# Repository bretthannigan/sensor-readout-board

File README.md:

# Sensor Readout Board

This repository includes the software, firmware, and hardware for the readout electronics used in the paper:

> B. C. Hannigan, T. J. Cuthbert, C. Admadizadeh, and C. Menon, _Distributed Sensing Along Fibres for Smart Clothing_. April 2023. [Preprint]

## Python Client

The `Client` subfolder contains the source code for the PC client, written in Python. The client allows connection to the FPGA and optional logging of data. The data can be interpreted in a variety of formats, such as:
- `raw`: raw ADC counts (32-bit signed integer)
- `iq`: impedances expressed as in-phase and quadrature components (equivalently, real and imagingary impedance components) in Ohms.
- `magphase`: impedances expressed as magnitude (in dB) and phase (in degrees).
- `RCseries`: impedances converted to resistance and capacitance values in an RC series circuit.
- `RCparallel`: impedances converted to resistance and capacitance values in an RC parallel circuit.
- `model`: (experimental) processed signals using a provided model (e.g., from sklearn or Keras) to convert the raw signals into a measure of interest.
Command-line arguments exist to control the COM port and logfile destination. One can also enable or disable the plotting of data to the screen and triggering ability. Note that the correct gain that matches the jumper on the PCB must be supplied via command-line argument for the scaling to be correct. There also exist some calibration curves as Excel spreadsheets.

## FPGA Firmware

The `Firmware` folder contains many general-purpose logic buliding blocks such as counters, FIFOs, memories, etc. and associated test-benches. The `Firmware/top` subfolder contains the top-level Verilog file `top.v` which was used for the data collection in the paper. This relies directly on the following third-party libraries:
- `verilog-lfsr` by Alex Forencich: https://github.com/alexforencich/verilog-lfsr. Used to implement the linear-feedback shift register that enables redundancy checking for the MIN protocol serial packets.
- `osdvu/uart` by Timothy Goddard: https://github.com/cyrozap/osdvu. Used to implement the UART.
- `min-protocol` by Ken Tindell: https://github.com/min-protocol/min. Used to frame the data sent to the PC.

## Hardware

The `Hardware/Enclosure` subfolder contains Solidworks files for the system enclosure. These were printed on a FDM 3D printer. The `Hardware/PCB` subfolder contains PCB schematic and layout files from KiCAD. The other subfolders contain (disorganized) SPICE simulations, previous iterations, and other files used during development.

©2023 ETH Zurich, Brett Hannigan; D-HEST; Biomedical and Mobile Health Technology (BMHT) Lab; Carlo Menon

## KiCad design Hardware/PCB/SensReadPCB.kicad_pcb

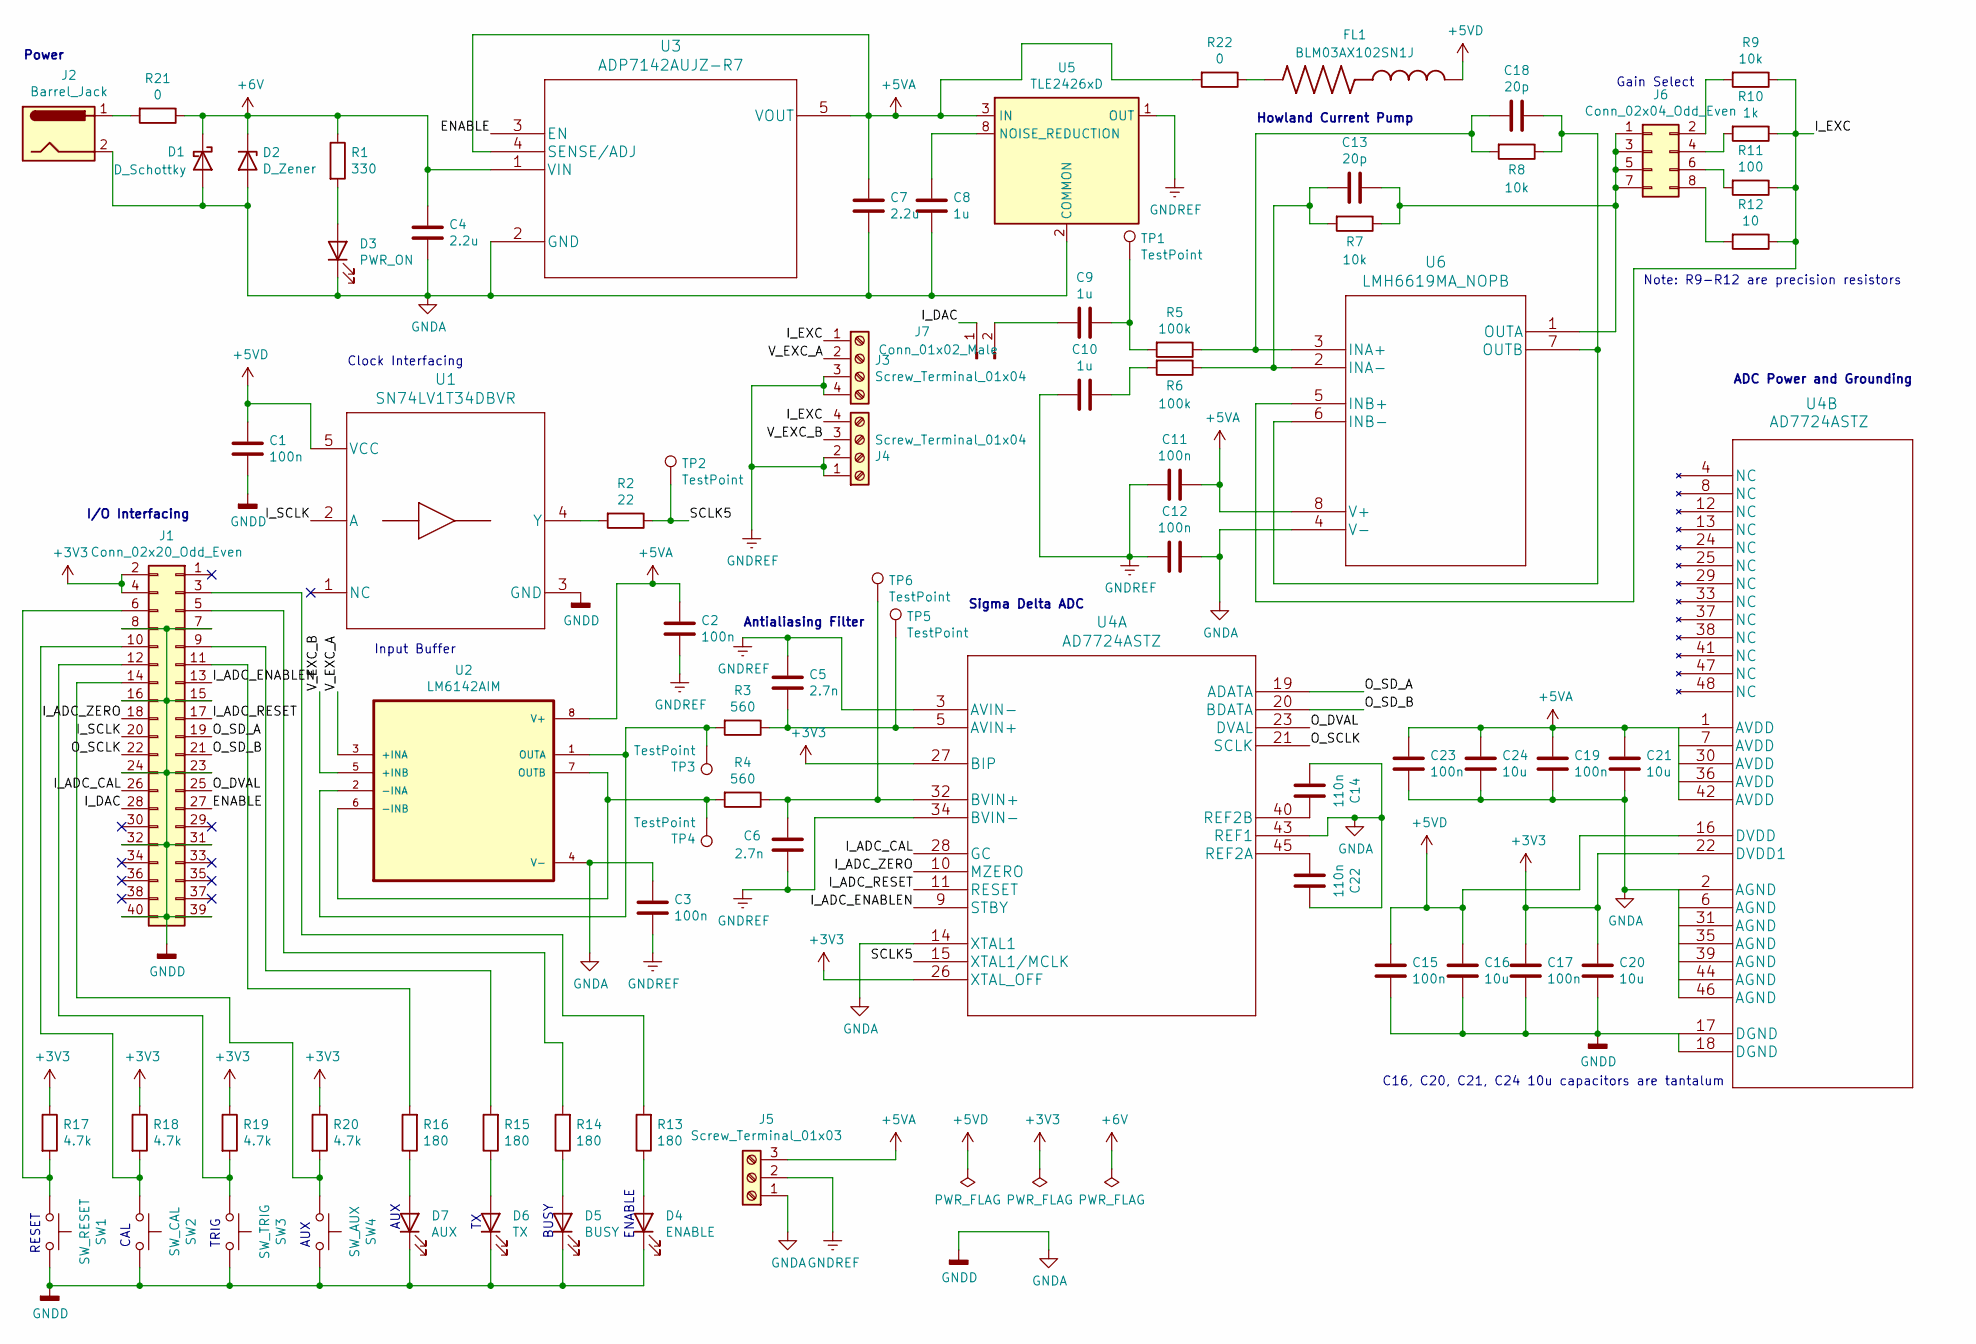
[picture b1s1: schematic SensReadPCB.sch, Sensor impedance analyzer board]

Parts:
C1, C2, C3, C11, C12, C15, C17, C19, C23: 100n; C_0603_1608Metric_Pad1.08x0.95mm_HandSolder
C4, C7: 2.2u; C_0603_1608Metric_Pad1.08x0.95mm_HandSolder
C5, C6: 2.7n; C_0603_1608Metric_Pad1.08x0.95mm_HandSolder
C8, C9, C10: 1u; C_0603_1608Metric_Pad1.08x0.95mm_HandSolder
C13, C18: 20p; C_0603_1608Metric_Pad1.08x0.95mm_HandSolder
C14, C22: 110n; C_0603_1608Metric_Pad1.08x0.95mm_HandSolder
C16, C20, C21, C24: 10u; C_0603_1608Metric_Pad1.08x0.95mm_HandSolder
D1: D_Schottky; D_SOD-323_HandSoldering
D2: D_Zener; D_SOD-323_HandSoldering
D3: PWR_ON; D_0603_1608Metric_Pad1.05x0.95mm_HandSolder
D4: ENABLE; D_0603_1608Metric_Pad1.05x0.95mm_HandSolder
D5: BUSY; D_0603_1608Metric_Pad1.05x0.95mm_HandSolder
D6: TX; D_0603_1608Metric_Pad1.05x0.95mm_HandSolder
D7: AUX; D_0603_1608Metric_Pad1.05x0.95mm_HandSolder
FL1: BLM03AX102SN1J; BEADC0603X33N
J1: Conn_02x20_Odd_Even; PinHeader_2x20_P2.54mm_Vertical
J2: Barrel_Jack; KLDX-0202-A
J3, J4: Screw_Terminal_01x04; TerminalBlock_Phoenix_MPT-0,5-4-2.54_1x04_P2.54mm_Horizontal
J5: Screw_Terminal_01x03; PinSocket_1x03_P2.54mm_Vertical
J6: Conn_02x04_Odd_Even; PinHeader_2x04_P2.54mm_Vertical
J7: Conn_01x02_Male; PinHeader_1x02_P2.54mm_Vertical
R1: 330; R_0603_1608Metric_Pad0.98x0.95mm_HandSolder
R2: 22; R_0603_1608Metric_Pad0.98x0.95mm_HandSolder
R3, R4: 560; R_0603_1608Metric_Pad0.98x0.95mm_HandSolder
R5, R6: 100k; R_0603_1608Metric_Pad0.98x0.95mm_HandSolder
R7, R8, R9: 10k; R_0603_1608Metric_Pad0.98x0.95mm_HandSolder
R10: 1k; R_0603_1608Metric_Pad0.98x0.95mm_HandSolder
R11: 100; R_0603_1608Metric_Pad0.98x0.95mm_HandSolder
R12: 10; R_0603_1608Metric_Pad0.98x0.95mm_HandSolder
R13, R14, R15, R16: 180; R_0603_1608Metric_Pad0.98x0.95mm_HandSolder
R17, R18, R19, R20: 4.7k; R_0603_1608Metric_Pad0.98x0.95mm_HandSolder
R21, R22: 0; R_0603_1608Metric_Pad0.98x0.95mm_HandSolder
SW1: SW_RESET; PTS636_SMTR
SW2: SW_CAL; PTS636_SMTR
SW3: SW_TRIG; PTS636_SMTR
SW4: SW_AUX; PTS636_SMTR
TP1, TP2, TP3, TP4, TP5, TP6: TestPoint; TestPoint_THTPad_2.5x2.5mm_Drill1.2mm
U1: SN74LV1T34DBVR
U2: LM6142AIM
U3: ADP7142AUJZ-R7
U4: AD7724ASTZ
U5: TLE2426xD; SOIC-8_3.9x4.9mm_P1.27mm
U6: LMH6619MA_NOPB; LMH6619MA

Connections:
+3V3: C17.1, C20.1, J1.2, J1.4, R17.1, R18.1, R19.1, R20.1, U4.22 (DVDD1), U4.26 (XTAL_OFF), U4.27 (BIP)
+5VA: C2.1, C7.1, C11.1, C19.1, C21.1, C23.1, C24.1, J5.3, R22.2, U2.8 (V+), U3.4 (SENSE/ADJ), U3.5 (VOUT), U4.1 (AVDD), U4.7 (AVDD), U4.30 (AVDD), U4.36 (AVDD), U4.42 (AVDD), U5.3 (IN), U6.8 (V+)
+5VD: C1.1, C15.1, C16.1, FL1.1, U1.5 (VCC), U4.16 (DVDD)
+6V: C4.1, D1.1 (K), D2.1 (K), R1.1, R21.1, U3.1 (VIN)
/ENABLE: J1.27, U3.3 (EN)
/I_ADC_CAL: J1.26, U4.28 (GC)
/I_ADC_ENABLEN: J1.13, U4.9 (STBY)
/I_ADC_RESET: J1.17, U4.11 (RESET)
/I_ADC_ZERO: J1.18, U4.10 (MZERO)
/I_DAC: J1.28, J7.1
/I_EXC: J3.1, J4.4, R9.1, R10.1, R11.1, R12.1, U6.5 (INB+)
/I_SCLK: J1.20, U1.2 (A)
/O_DVAL: J1.25, U4.23 (DVAL)
/O_SCLK: J1.22, U4.21 (SCLK)
/O_SD_A: J1.19, U4.19 (ADATA)
/O_SD_B: J1.21, U4.20 (BDATA)
/SCLK5: R2.1, TP2.1, U4.15 (XTAL1/MCLK)
/V_EXC_A: J3.2, U2.3 (+INA)
/V_EXC_B: J4.3, U2.5 (+INB)
GNDA: C1.2, C3.1, C4.2, C7.2, C8.2, C12.1, C14.2, C15.2, C16.2, C17.2, C19.2, C20.2, C21.2, C22.1, C23.2, C24.2, D1.2 (A), D2.2 (A), D3.1 (K), D4.1 (K), D5.1 (K), D6.1 (K), D7.1 (K), J1.7, J1.8, J1.15, J1.16, J1.23, J1.24, J1.31, J1.32, J1.39, J1.40, J2.2, J5.1, SW1.2, SW2.2, SW3.2, SW4.2, U1.3 (GND), U2.4 (V-), U3.2 (GND), U4.2 (AGND), U4.6 (AGND), U4.14 (XTAL1), U4.17 (DGND), U4.18 (DGND), U4.31 (AGND), U4.35 (AGND), U4.39 (AGND), U4.43 (REF1), U4.44 (AGND), U4.46 (AGND), U5.2 (COMMON), U6.4 (V-)
GNDREF: C2.2, C3.2, C5.1, C6.2, C10.2, C11.2, C12.2, J3.3, J3.4, J4.1, J4.2, J5.2, U4.3 (AVIN-), U4.34 (BVIN-), U5.1 (OUT)
unnamed: C5.2, R3.1, TP5.1, U4.5 (AVIN+)
unnamed: C6.1, R4.1, TP6.1, U4.32 (BVIN+)
unnamed: C8.1, U5.8 (NOISE_REDUCTION)
unnamed: C9.1, R5.2, TP1.1
unnamed: C9.2, J7.2
unnamed: C10.1, R6.2
unnamed: C13.1, J6.1, J6.3, J6.5, J6.7, R7.1, U6.1 (OUTA)
unnamed: C13.2, R6.1, R7.2, U6.2 (INA-)
unnamed: C14.1, U4.40 (REF2B)
unnamed: C18.1, R8.1, U6.6 (INB-), U6.7 (OUTB)
unnamed: C18.2, R5.1, R8.2, U6.3 (INA+)
unnamed: C22.2, U4.45 (REF2A)
unnamed: D3.2 (A), R1.2
unnamed: D4.2 (A), R13.1
unnamed: D5.2 (A), R14.1
unnamed: D6.2 (A), R15.1
unnamed: D7.2 (A), R16.1
unnamed: FL1.2, R22.1
unnamed: J1.3, R13.2
unnamed: J1.5, R14.2
unnamed: J1.6, R17.2, SW1.1
unnamed: J1.9, R15.2
unnamed: J1.10, R18.2, SW2.1
unnamed: J1.11, R16.2
unnamed: J1.12, R19.2, SW3.1
unnamed: J1.14, R20.2, SW4.1
unnamed: J2.1, R21.2
unnamed: J6.2, R9.2
unnamed: J6.4, R10.2
unnamed: J6.6, R11.2
unnamed: J6.8, R12.2
unnamed: R2.2, U1.4 (Y)
unnamed: R3.2, TP3.1, U2.1 (OUTA), U2.2 (-INA)
unnamed: R4.2, TP4.1, U2.6 (-INB), U2.7 (OUTB)

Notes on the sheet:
Sigma Delta ADC
Antialiasing Filter
ADC Power and Grounding
Howland Current Pump
Power
Clock Interfacing
Input Buffer
I/O Interfacing
Note: R9-R12 are precision resistors
ENABLE
BUSY
TRIG
CAL
RESET
AUX
Gain Select
C16, C20, C21, C24 10u capacitors are tantalum

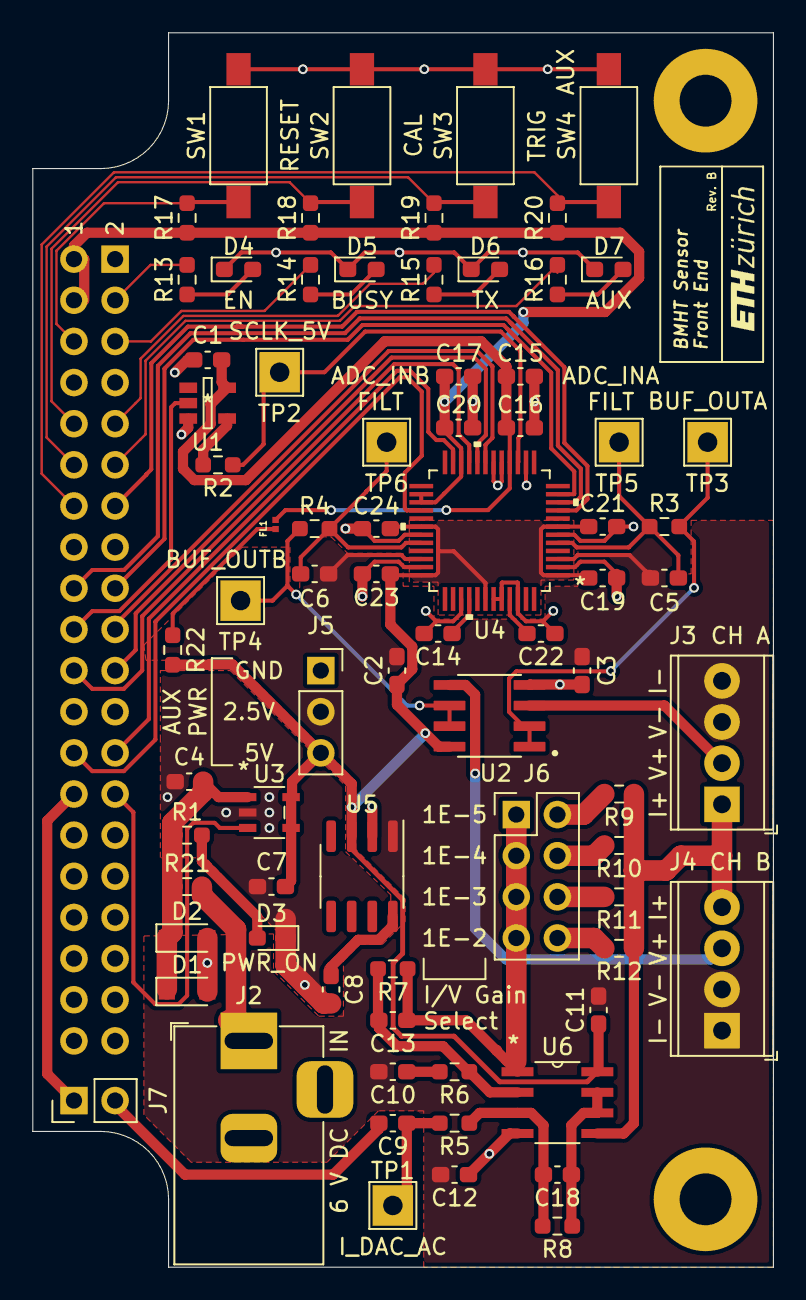
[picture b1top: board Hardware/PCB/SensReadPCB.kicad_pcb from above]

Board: 2 copper layers, 45.7 x 76.2 mm, 77 parts (1 on the bottom side), 55 nets.

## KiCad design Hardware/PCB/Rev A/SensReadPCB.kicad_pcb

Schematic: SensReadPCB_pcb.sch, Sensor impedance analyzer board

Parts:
C1, C2: 20p; C_1206_HandSoldering
C3, C4, C5, C8, C9, C19, C20: 100n; C_1206_HandSoldering
C6, C11: 1u; C_1206_HandSoldering
C7, C10: 10n; C_1206_HandSoldering
C12: 680p; C_1206_HandSoldering
C13: 1.5n; C_1206_HandSoldering
C14, C15, C16: 130p; C_1206_HandSoldering
C17: 390p; C_1206_HandSoldering
C18: C; C_1206_HandSoldering
D1, D3: D_Schottky; D_1206
D2, D6: D_Zener; D_1206
D4: PWR_ON; LED_1206_HandSoldering
D5: ENABLE; LED_1206_HandSoldering
J1: Barrel_Jack; BARREL_JACK
J2: Conn_02x20_Odd_Even; Pin_Header_Straight_2x20_Pitch2.54mm
J3: Conn_02x04_Odd_Even; Pin_Header_Straight_2x04_Pitch2.54mm
J4: Screw_Terminal_01x04; TerminalBlock_Phoenix_MPT-2.54mm_4pol
R1, R2: 100k; R_1206_HandSoldering
R3, R4, R5: 10k; R_1206_HandSoldering
R6, R18: 1k; R_1206_HandSoldering
R7: 100; R_1206_HandSoldering
R8: 10; R_1206_HandSoldering
R9: 4.75k; R_1206_HandSoldering
R10: 13.7k; R_1206_HandSoldering
R11: 14.0k; R_1206_HandSoldering
R12: 750; R_1206_HandSoldering
R13: 806; R_1206_HandSoldering
R14: 4.64k; R_1206_HandSoldering
R15: 1.10k; R_1206_HandSoldering
R16: 6.98k; R_1206_HandSoldering
R17: 68; R_1206_HandSoldering
R19: 510; R_1206_HandSoldering
R20, R21: 0R; R_1206_HandSoldering
R22, R29: 0; R_1206_HandSoldering
R23: 5.11k; R_1206_HandSoldering
R24, R27: 28k; R_1206_HandSoldering
R25: 1.58meg; R_1206_HandSoldering
R26: 68.1k; R_1206_HandSoldering
R28: 5.36k; R_1206_HandSoldering
RV1: 10k; 23BR50KLFTR
RV2: 47k; 23BR50KLFTR
TP1: DAC_AC; Measurement_Point_Square-TH_Big
TP2: LF_1; Measurement_Point_Square-TH_Big
TP3: LF_2; Measurement_Point_Square-TH_Big
TP4: LF_3; Measurement_Point_Square-TH_Big
TP5: LF_4; Measurement_Point_Square-TH_Big
TP6: ADC_OUT; Measurement_Point_Square-TH_Big
TP7, TP8: TestPoint; Measurement_Point_Square-TH_Big
U1: LMH6619MA_NOPB; LMH6619MA&slash_NOPB
U2: MAX903CSA+; MAX903CSA&plus_
U3: LP2985A-10DBVR
U4: TLE2426xD; TLE2426CD
U5: LM6144AIM_NOPB; LM6144AIM&slash_NOPB

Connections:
+3V3: C3.1, J2.2, J2.4, U2.5, U2.8
+5V: C6.1, D1.1 (K), D2.1 (K), J1.1, R19.1, U3.1
+5VA: C4.1, C8.1, C10.1, C19.1, U1.8, U2.1, U3.5, U4.3 (IN), U5.4
-5V: C5.1, C6.2, C7.2, C9.1, C10.2, C11.2, C20.1, D1.2 (A), D2.2 (A), D4.1 (K), J1.2, U1.4, U2.4, U3.2, U4.2 (COMMON), U5.11
/ADC_2_Y: C13.2, R14.1, R21.2, R29.2, TP4.1, U5.8
/ADC_4_Y: C14.2, R20.2, R24.1, R25.2, TP5.1, U5.14
/ADC_FB_N: J2.6, RV2.2
/ADC_FB_P: J2.5, RV1.1
/ADC_FB_S_N: C12.2, R9.2, R11.2, R14.2, RV1.2, TP7.1, U5.2
/ADC_FB_S_P: RV2.3, TP8.1, U5.3
/ADC_OUT: J2.3, R18.2, TP6.1, U2.7
/CLK: J2.10
/DAC_IN: C18.2, J2.11
/ENABLE: J2.1, R17.2, U3.3
/I_EXC: J4.1, R5.1, R6.1, R7.1, R8.1, U1.5
/S_CLK: J2.9
/V_EXC: J4.2, R9.1, R10.2, R16.1
GNDA: C3.2, C4.2, C5.2, C8.2, C9.2, C17.1, C19.2, C20.2, D3.2 (A), D5.1 (K), D6.2 (A), J2.7, J2.8, J4.3, J4.4, R2.2, R22.2, R23.1, RV2.1, U2.3, U2.6, U4.1 (OUT), U5.5, U5.10, U5.12
unnamed: C1.1, J3.1, J3.3, J3.5, J3.7, R3.1, U1.1
unnamed: C1.2, R2.1, R3.2, U1.2
unnamed: C2.1, R4.1, U1.6, U1.7
unnamed: C2.2, R1.1, R4.2, U1.3
unnamed: C7.1, U3.4
unnamed: C11.1, U4.8 (NOISE_REDUCTION)
unnamed: C12.1, R11.1, R12.2, TP2.1, U5.1
unnamed: C13.1, R15.1, R16.2, U5.9
unnamed: C14.1, C15.1, C16.2, R23.2, R26.2
unnamed: C15.2, R26.1, R28.1, R29.1
unnamed: C16.1, R22.1, R25.1, R27.2, U5.13
unnamed: C17.2, R24.2, R27.1, R28.2
unnamed: C18.1, R1.2, TP1.1
unnamed: D3.1 (K), D6.1 (K), R18.1
unnamed: D4.2 (A), R19.2
unnamed: D5.2 (A), R17.1
unnamed: J3.2, R5.2
unnamed: J3.4, R6.2
unnamed: J3.6, R7.2
unnamed: J3.8, R8.2
unnamed: R10.1, R12.1, R13.1, U5.6
unnamed: R13.2, R15.2, TP3.1, U5.7
unnamed: R20.1, R21.1, U2.2

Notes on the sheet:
Gain Select
Howland Current Source
Power Conditioning
Interfacing
Comparator
Single-amplifier biquad
ADC Loop Filter
Fleisher-Tow biquad
Set: R21 15k R32 32k
Set: R21 4.7k

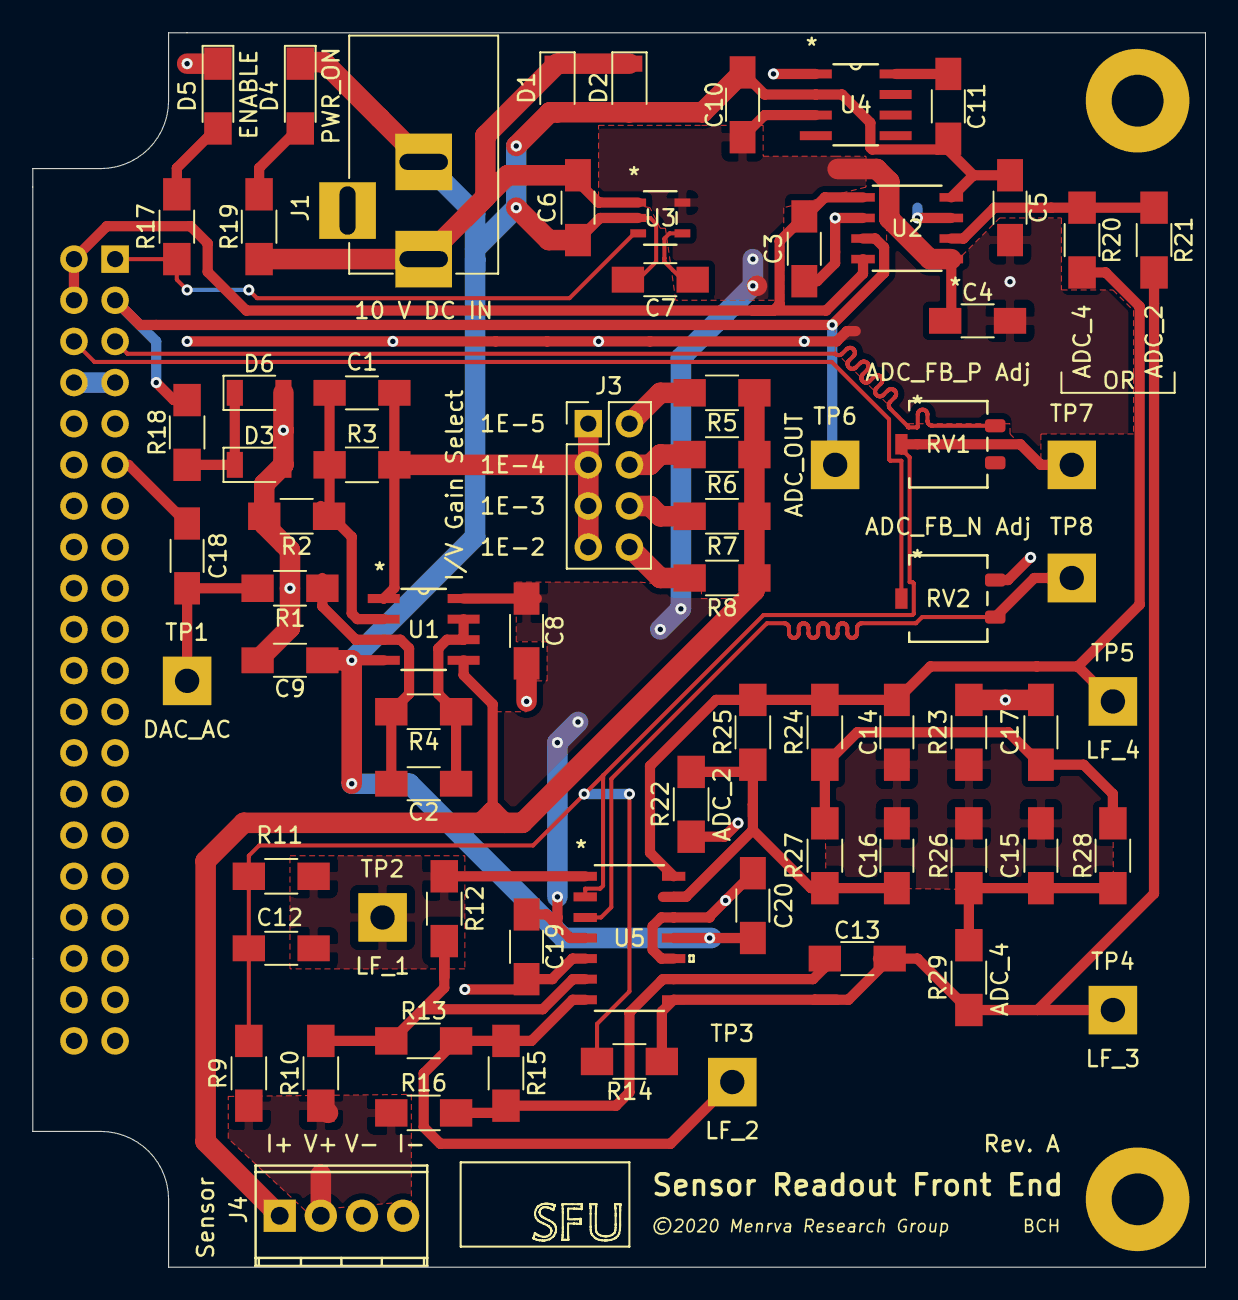
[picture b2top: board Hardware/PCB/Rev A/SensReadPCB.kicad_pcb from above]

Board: 2 copper layers, 72.4 x 76.2 mm, 74 parts (1 on the bottom side), 39 nets.

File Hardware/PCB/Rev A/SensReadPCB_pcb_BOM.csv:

Reference, Value, Footprint, Datasheet,Done
U1,LMH6619MA_NOPB,LMH6619MA:LMH6619MA&slash_NOPB,,TRUE
R1,100k,Resistors_SMD:R_1206_HandSoldering,~,TRUE
R2,100k,Resistors_SMD:R_1206_HandSoldering,~,TRUE
R3,10k,Resistors_SMD:R_1206_HandSoldering,~,TRUE
C1,20p,Capacitors_SMD:C_1206_HandSoldering,~,TRUE
R4,10k,Resistors_SMD:R_1206_HandSoldering,~,TRUE
C2,20p,Capacitors_SMD:C_1206_HandSoldering,~,TRUE
J3,Conn_02x04_Odd_Even,Pin_Headers:Pin_Header_Straight_2x04_Pitch2.54mm,~,TRUE
R5,10k,Resistors_SMD:R_1206_HandSoldering,~,TRUE
R6,1k,Resistors_SMD:R_1206_HandSoldering,~,TRUE
R7,100,Resistors_SMD:R_1206_HandSoldering,~,TRUE
R8,10,Resistors_SMD:R_1206_HandSoldering,~,TRUE
C9,100n,Capacitors_SMD:C_1206_HandSoldering,~,TRUE
U4,TLE2426xD,TLE2426CD:TLE2426CD,http://www.ti.com/lit/ds/symlink/tle2426.pdf,TRUE
C11,1u,Capacitors_SMD:C_1206_HandSoldering,~,TRUE
U3,LP2985A-10DBVR,LP2985A10DBVR:LP2985A-10DBVR,,TRUE
C6,1u,Capacitors_SMD:C_1206_HandSoldering,~,TRUE
C10,10n,Capacitors_SMD:C_1206_HandSoldering,~,TRUE
C7,10n,Capacitors_SMD:C_1206_HandSoldering,~,TRUE
U2,MAX903CSA+,MAX903CSA:MAX903CSA&plus_,,TRUE
C4,100n,Capacitors_SMD:C_1206_HandSoldering,~,TRUE
C8,100n,Capacitors_SMD:C_1206_HandSoldering,~,TRUE
C5,100n,Capacitors_SMD:C_1206_HandSoldering,~,TRUE
C3,100n,Capacitors_SMD:C_1206_HandSoldering,~,TRUE
TP1,DAC_AC,Measurement_Points:Measurement_Point_Square-TH_Big,~,#N/A
R16,6.98k,Resistors_SMD:R_1206_HandSoldering,~,TRUE
R14,4.64k,Resistors_SMD:R_1206_HandSoldering,~,TRUE
R15,1.10k,Resistors_SMD:R_1206_HandSoldering,~,TRUE
C13,1.5n,Capacitors_SMD:C_1206_HandSoldering,~,TRUE
TP6,ADC_OUT,Measurement_Points:Measurement_Point_Square-TH_Big,~,#N/A
J1,Barrel_Jack,Connectors:BARREL_JACK,~,TRUE
R19,510,Resistors_SMD:R_1206_HandSoldering,~,TRUE
D4,PWR_ON,LEDs:LED_1206_HandSoldering,~,TRUE
D1,D_Schottky,Diodes_SMD:D_1206,~,TRUE
D3,D_Schottky,Diodes_SMD:D_1206,~,TRUE
D6,D_Zener,Diodes_SMD:D_1206,~,TRUE
R18,1k,Resistors_SMD:R_1206_HandSoldering,~,TRUE
D2,D_Zener,Diodes_SMD:D_1206,~,TRUE
D5,ENABLE,LEDs:LED_1206_HandSoldering,~,TRUE
R17,68,Resistors_SMD:R_1206_HandSoldering,~,TRUE
R24,28k,Resistors_SMD:R_1206_HandSoldering,~,#N/A
R27,28k,Resistors_SMD:R_1206_HandSoldering,~,#N/A
C14,130p,Capacitors_SMD:C_1206_HandSoldering,~,#N/A
C16,130p,Capacitors_SMD:C_1206_HandSoldering,~,#N/A
R25,1.58meg,Resistors_SMD:R_1206_HandSoldering,~,#N/A
C15,130p,Capacitors_SMD:C_1206_HandSoldering,~,#N/A
R26,68.1k,Resistors_SMD:R_1206_HandSoldering,~,#N/A
R23,5.11k,Resistors_SMD:R_1206_HandSoldering,~,#N/A
C17,390p,Capacitors_SMD:C_1206_HandSoldering,~,#N/A
TP5,LF_4,Measurement_Points:Measurement_Point_Square-TH_Big,~,#N/A
R20,0R,Resistors_SMD:R_1206_HandSoldering,~,TRUE
R21,0R,Resistors_SMD:R_1206_HandSoldering,~,TRUE
R22,0,Resistors_SMD:R_1206_HandSoldering,~,TRUE
R29,0,Resistors_SMD:R_1206_HandSoldering,~,TRUE
R28,5.36k,Resistors_SMD:R_1206_HandSoldering,~,TRUE
C20,100n,Capacitors_SMD:C_1206_HandSoldering,~,TRUE
C18,C,Capacitors_SMD:C_1206_HandSoldering,~,
TP4,LF_3,Measurement_Points:Measurement_Point_Square-TH_Big,~,#N/A
RV2,47k,23BR50KLFTR:23BR50KLFTR,~,TRUE
C19,100n,Capacitors_SMD:C_1206_HandSoldering,~,TRUE
R10,13.7k,Resistors_SMD:R_1206_HandSoldering,~,TRUE
TP3,LF_2,Measurement_Points:Measurement_Point_Square-TH_Big,~,#N/A
TP2,LF_1,Measurement_Points:Measurement_Point_Square-TH_Big,~,#N/A
RV1,10k,23BR50KLFTR:23BR50KLFTR,~,TRUE
R13,806,Resistors_SMD:R_1206_HandSoldering,~,TRUE
R12,750,Resistors_SMD:R_1206_HandSoldering,~,TRUE
R11,14.0k,Resistors_SMD:R_1206_HandSoldering,~,TRUE
C12,680p,Capacitors_SMD:C_1206_HandSoldering,~,TRUE
R9,4.75k,Resistors_SMD:R_1206_HandSoldering,~,TRUE
U5,LM6144AIM_NOPB,LM6144AIM:LM6144AIM&slash_NOPB,,TRUE
TP8,TestPoint,Measurement_Points:Measurement_Point_Square-TH_Big,~,#N/A
TP7,TestPoint,Measurement_Points:Measurement_Point_Square-TH_Big,~,#N/A
J4,Screw_Terminal_01x04,TerminalBlocks_Phoenix:TerminalBlock_Phoenix_MPT-2.54mm_4pol,~,TRUE
J2,Conn_02x20_Odd_Even,Pin_Headers:Pin_Header_Straight_2x20_Pitch2.54mm,~,TRUE
,,,,56

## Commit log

2021-09-29 Add files for Rev. A prototype
2021-09-29 Add .gitignore, .gitattributes
2021-09-30 Add files for RevB PCB.
2021-10-21 Redefined I/O pins for RevB board
2021-10-21 Enclosure design added.
2021-10-27 Temporary changes to FW for testing RevB
2021-11-02 Data readout working with RevB board.
2021-11-02 Readout working with RevB board.
2022-02-09 top_1f working. Modified sine_lut to separate 1/4-wave logic.
2022-04-21 client: multiple channel graphing, thread lock
2022-05-11 ReadSensor working with arbitrary # of channels
2022-05-31 Calibration and client changes.
2022-06-01 Changes to allow triggered logging.
2022-06-02 4 frequency verilog code + client on bmht31-13-92
2022-06-07 Client: timestamp since trigger, TSV file
2022-06-07 git ignore tsv datalogs
2022-06-08 Versions used for data collection #2 on 2022-06-08
2022-07-22 Custom model support for client
2022-08-08 Fixed error in IQ mode.
2022-08-08 Fixed error in IQ mode (2)
2023-04-11 Version used for paper
2023-04-20 Addition of Readme and licence infomation.
2023-04-20 Minor fix to Readme
2023-04-20 Remove too large file model.sav
2023-04-20 Edit Readme.md

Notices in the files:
Hardware/PCB/Rev A/SensReadPCB.kicad_pcb:
©2020 Menrva Research Group
Hardware/PCB/SensReadPCB.kicad_pcb:
©2021 BCH
parts and their libraries:
Copyright 2016 Accelerated Designs. All rights reserved.
Copyright 2021 Accelerated Designs. All rights reserved.
